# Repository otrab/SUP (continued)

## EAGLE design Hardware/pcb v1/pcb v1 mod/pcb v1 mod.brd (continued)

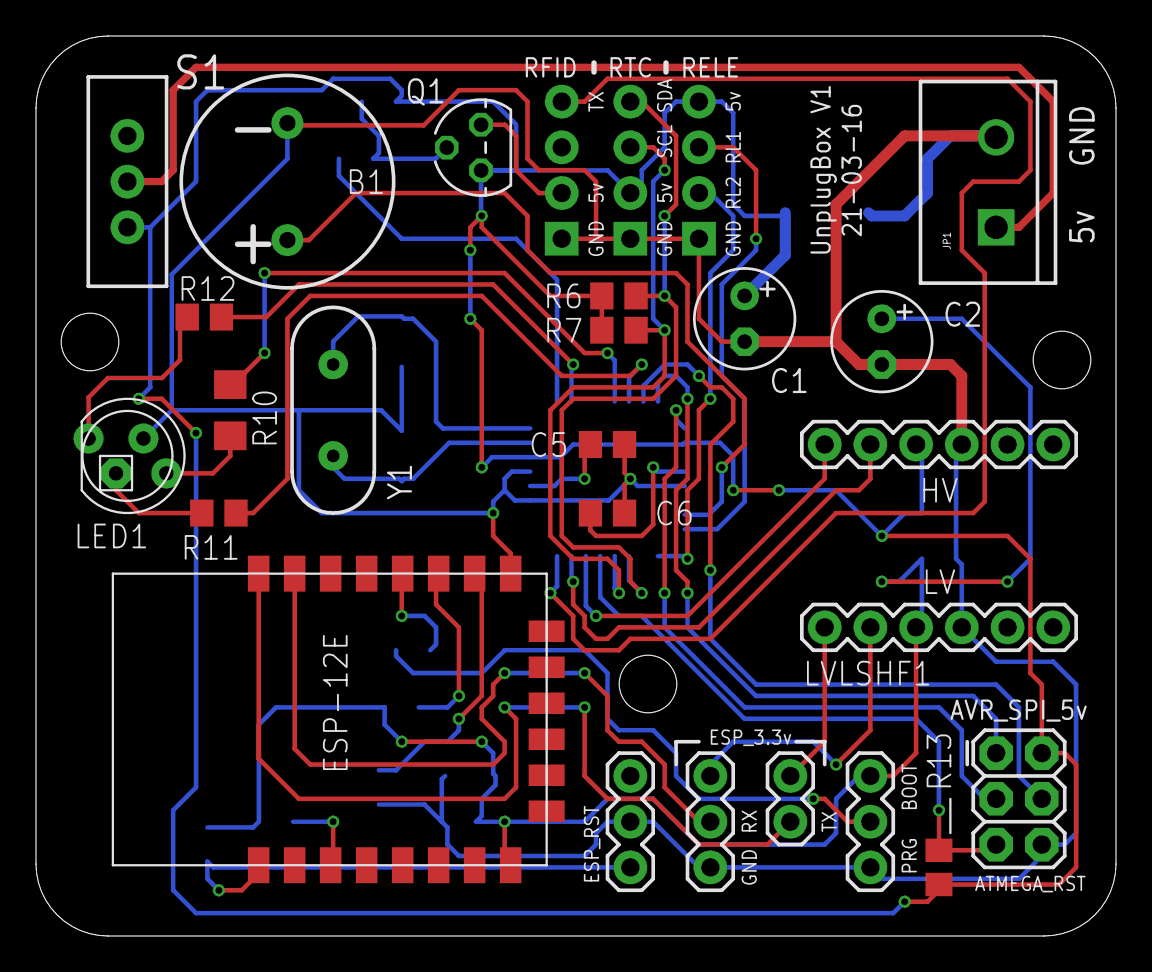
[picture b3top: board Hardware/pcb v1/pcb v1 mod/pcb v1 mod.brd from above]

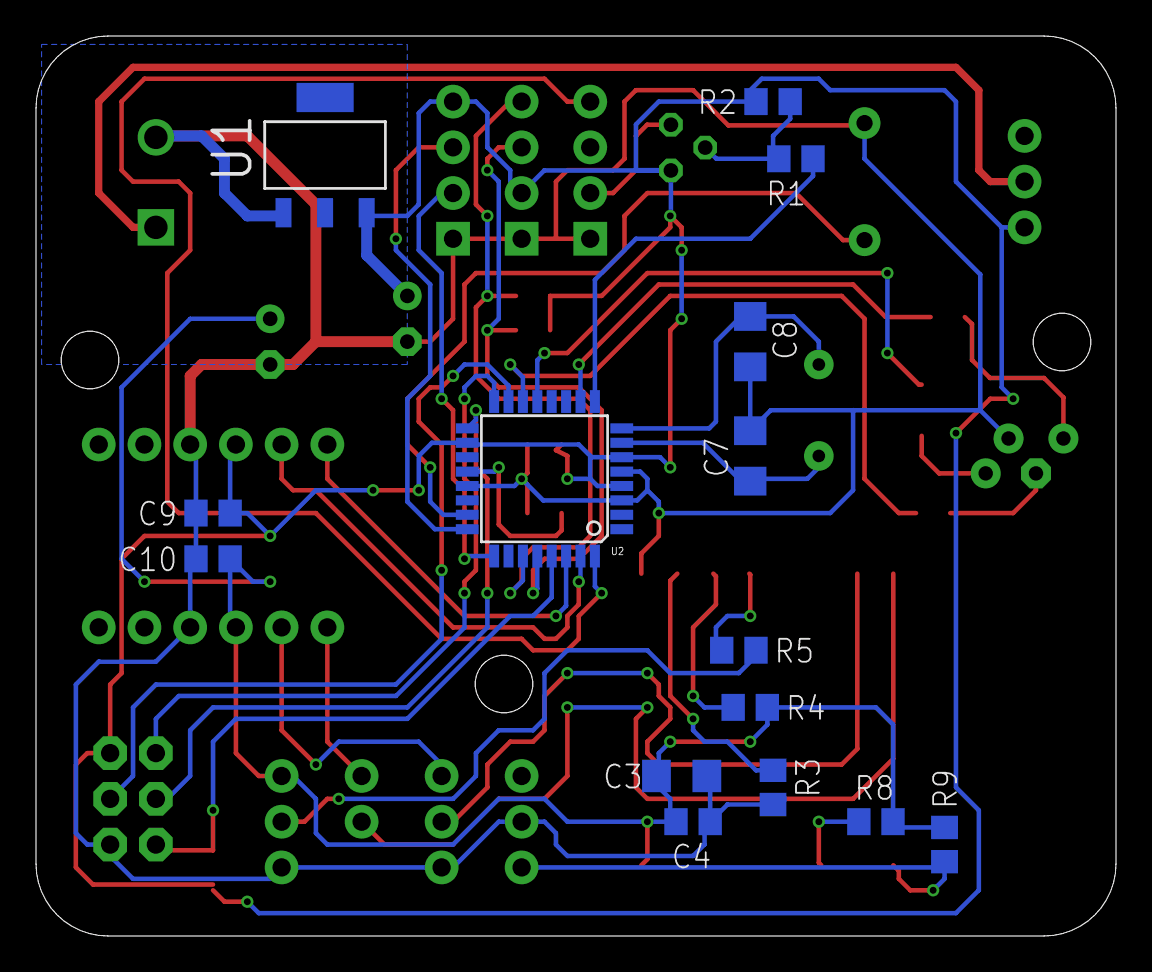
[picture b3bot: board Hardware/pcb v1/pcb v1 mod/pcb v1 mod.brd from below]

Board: 2 copper layers, 60.0 x 50.0 mm, 41 parts (15 on the bottom side), 38 nets.

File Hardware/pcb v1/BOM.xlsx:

Qty | Value | Device | Package | Parts | Description | Link
1 |  | ESP8266-12EESP8266-ESP12E | ESP8266-ESP12E | MDL1 | ESP8266-12E with additional I/O and GPIO04/05 corrected
3 |  | M03PTH | 1X03 | JP3, JP7, JP8 | Header 3
3 |  | M041X04_NO_SILK | 1X04_NO_SILK | JP2, JP4, JP5 | Header 4
1 |  | SWITCH-SPDTPTH | SWITCH-SPDT | S1 | SPDT Switch
1 | 100K | R-US_R0805 | R0805 | R13 | RESISTOR, American symbol
2 | 100R | R-US_R0805 | R0805 | R11, R12 | RESISTOR, American symbol
5 | 100nF | C-USC0805 | C0805 | C4, C5, C6, C9, C10 | CAPACITOR, American symbol
9 | 10k | R-US_R0805 | R0805 | R1, R2, R3, R4, R5, R6, R7, R8, R9 | RESISTOR, American symbol
2 | 10uF | CPOL-USE2.5-6 | E2,5-6 | C1, C2 | POLARIZED CAPACITOR, American symbol
1 | 160R | R-US_R1206 | R1206 | R10 | RESISTOR, American symbol
1 | 16Mhz | CRYSTALHC49US | HC49US | Y1 | Various standard crystals. Proven footprints. Spark Fun Electronics SKU : COM-0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
1 | 1uF | C-USC1206 | C1206 | C3 | CAPACITOR, American symbol
2 | 22pF | C-USC1206 | C1206 | C7, C8 | CAPACITOR, American symbol
1 | 2N3906 | 2N3906 | TO92 | Q1 | PNP Transistor
1 | 5MMRGBLED | 5MMRGBLED | LED5MMRGB | LED1
1 | ADP3338AKCZ-3.3RL7 | ADP3338AKCZ-3.3RL7 | SOT230P700X180-4N | U1 | Low Dropout Regulator | http://olimex.cl/en_US/shop/product/regulador-de-voltaje-adp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
1 | ATMEGA328P | ATMEGA328_SMT | TQFP32-08 | U2 | 32-Pin Atmega328 part
1 | AVR_SPI_PRG_6PTH | AVR_SPI_PRG_6PTH | 2X3 | J1 | AVR ISP 6 Pin
1 | BUZZERPTH | BUZZERPTH | BUZZER-12MM | SG1 | Buzzer 12mm
1 | LEVELSHIFTER4 | LEVELSHIFTER4 | LEVELSHIFTER4 | LVLSHF1
1 | M025MM | M025MM | SCREWTERMINAL-5MM-2 | JP1 | Standard 2-pin 0.1 header. Use with"
1 | M02PTH | M02PTH | 1X02 | JP9 | Standard 2-pin 0.1 header. Use with"

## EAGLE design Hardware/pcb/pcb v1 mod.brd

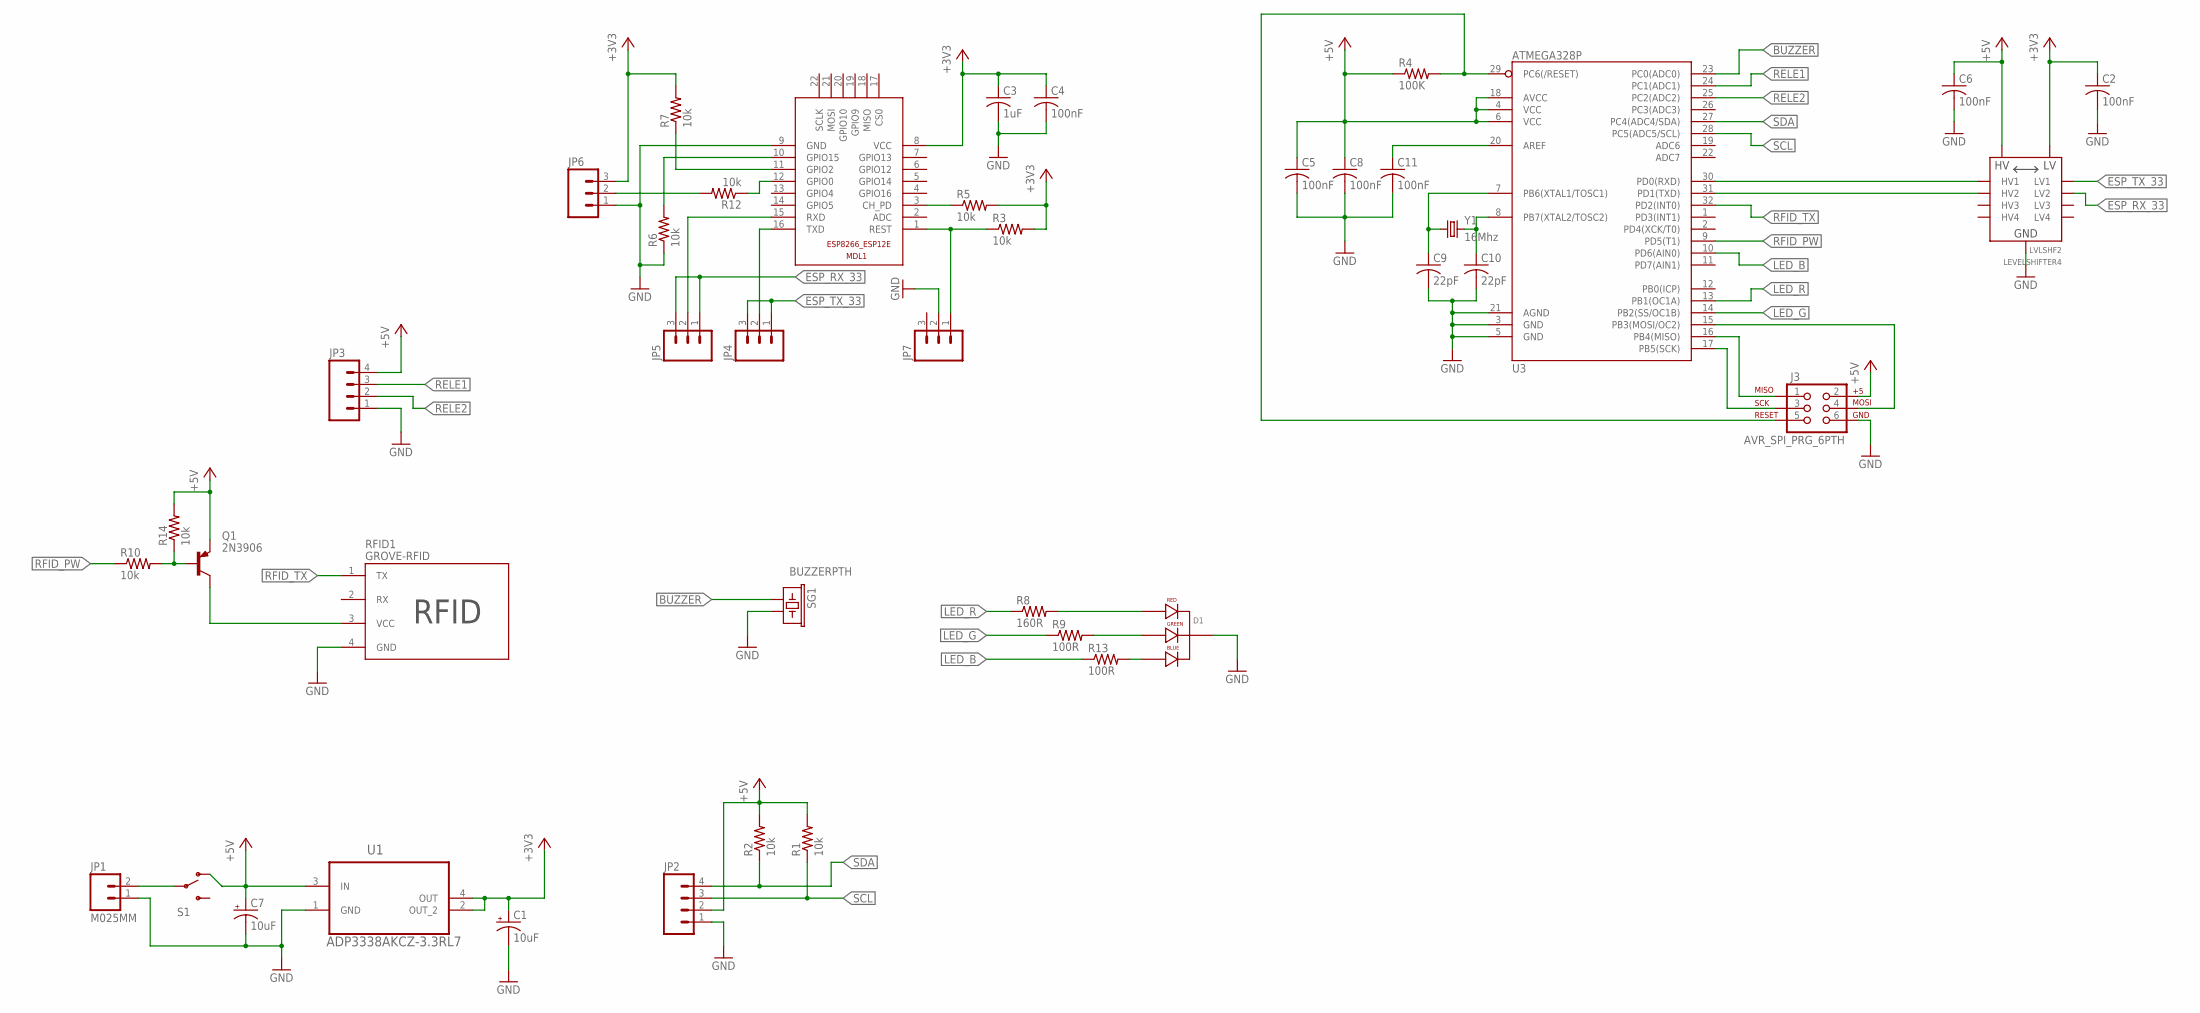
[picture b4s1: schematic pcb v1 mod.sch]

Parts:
C1, C7: 10uF; E2,5-6
C2, C4, C5, C6, C8, C11: 100nF; C0805
C3: 1uF; C1206
C9, C10: 22pF; C1206
D1: LED-RGB-CC-THRUCLEAR; LED-RGB-THRU
J3: AVR_SPI_PRG_6PTH; 2X3
JP1: M025MM; SCREWTERMINAL-5MM-2
JP2, JP3: M04PTH; 1X04
JP4, JP5, JP6, JP7: M03PTH; 1X03
LVLSHF2: LEVELSHIFTER4
MDL1: ESP8266-12EESP8266-ESP12E; ESP8266-ESP12E
Q1: 2N3906; TO92
R1, R2, R3, R5, R6, R7, R10, R12, R14: 10k; R0805
R4: 100K; R0805
R8: 160R; R1206
R9, R13: 100R; R0805
RFID1: GROVE-RFID
S1: SWITCH-SPDTPTH; SWITCH-SPDT
SG1: BUZZERPTH; BUZZER-12MM
U1: ADP3338AKCZ-3.3RL7; SOT230P700X180-4N
U3: ATMEGA328P; TQFP32-08
Y1: 16Mhz; HC49US

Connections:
+3V3: C1.+, C2.1, C3.1, C4.1, JP6.3, LVLSHF2.LV, MDL1.8 (VCC), R3.2, R5.2, R7.2, U1.2 (OUT_2), U1.4 (OUT)
+5V: C5.1, C6.1, C7.+, C8.1, J3.2, JP2.2, JP3.4, LVLSHF2.HV, Q1.3 (E), R1.2, R2.2, R4.1, R14.2, S1.1 (O), U1.3 (IN), U3.4 (VCC), U3.6 (VCC), U3.18 (AVCC)
BUZZER: SG1.+ (1), U3.23 (PC0(ADC0))
ESP_RX_33: JP5.1, JP5.3, LVLSHF2.LV2
ESP_TX_33: JP4.1, JP4.3, LVLSHF2.LV1
GND: C1.-, C2.2, C3.2, C4.2, C5.2, C6.2, C7.-, C8.2, C9.2, C10.2, C11.2, D1.2 (CATHODE), J3.6, JP1.1, JP2.1, JP3.1, JP6.1, JP7.2, LVLSHF2.GND, LVLSHF2.GND1 (GND), MDL1.9 (GND), R6.1, RFID1.4 (GND), SG1.- (2), U1.1 (GND), U3.3 (GND), U3.5 (GND), U3.21 (AGND)
LED_B: R13.1, U3.10 (PD6(AIN0))
LED_G: R9.1, U3.14 (PB2(SS/OC1B))
LED_R: R8.1, U3.13 (PB1(OC1A))
unnamed: JP1.2, S1.2
unnamed: MDL1.3 (CH_PD), R5.1
unnamed: MDL1.11 (GPIO2), R7.1
unnamed: MDL1.12 (GPIO0), R12.1
unnamed: MDL1.10 (GPIO15), R6.2
unnamed: JP5.2, MDL1.15 (RXD)
unnamed: Q1.2 (B), R10.2, R14.1
unnamed: JP4.2, MDL1.16 (TXD)
unnamed: JP7.1, MDL1.1 (REST), R3.1
unnamed: D1.1 (RED_CATHODE), R8.2
unnamed: C9.1, U3.7 (PB6(XTAL1/TOSC1)), Y1.1
unnamed: C10.1, U3.8 (PB7(XTAL2/TOSC2)), Y1.2
unnamed: C11.1, U3.20 (AREF)
unnamed: D1.3 (GREEN_CATHODE), R9.2
unnamed: D1.4 (BLUE_CATHODE), R13.2
unnamed: J3.3, U3.17 (PB5(SCK))
unnamed: J3.1, U3.16 (PB4(MISO))
unnamed: J3.4, U3.15 (PB3(MOSI/OC2))
unnamed: JP6.2, R12.2
unnamed: LVLSHF2.HV1, U3.30 (PD0(RXD))
unnamed: LVLSHF2.HV2, U3.31 (PD1(TXD))
unnamed: Q1.1 (C), RFID1.3 (VCC)
unnamed: J3.5, R4.2, U3.29 (PC6(/RESET))
RELE1: JP3.3, U3.24 (PC1(ADC1))
RELE2: JP3.2, U3.25 (PC2(ADC2))
RFID_PW: R10.1, U3.9 (PD5(T1))
RFID_TX: RFID1.1 (TX), U3.32 (PD2(INT0))
SCL: JP2.3, R1.1, U3.28 (PC5(ADC5/SCL))
SDA: JP2.4, R2.1, U3.27 (PC4(ADC4/SDA))

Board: 2 copper layers, 42 parts (0 on the bottom side), 38 nets, no tracks yet.

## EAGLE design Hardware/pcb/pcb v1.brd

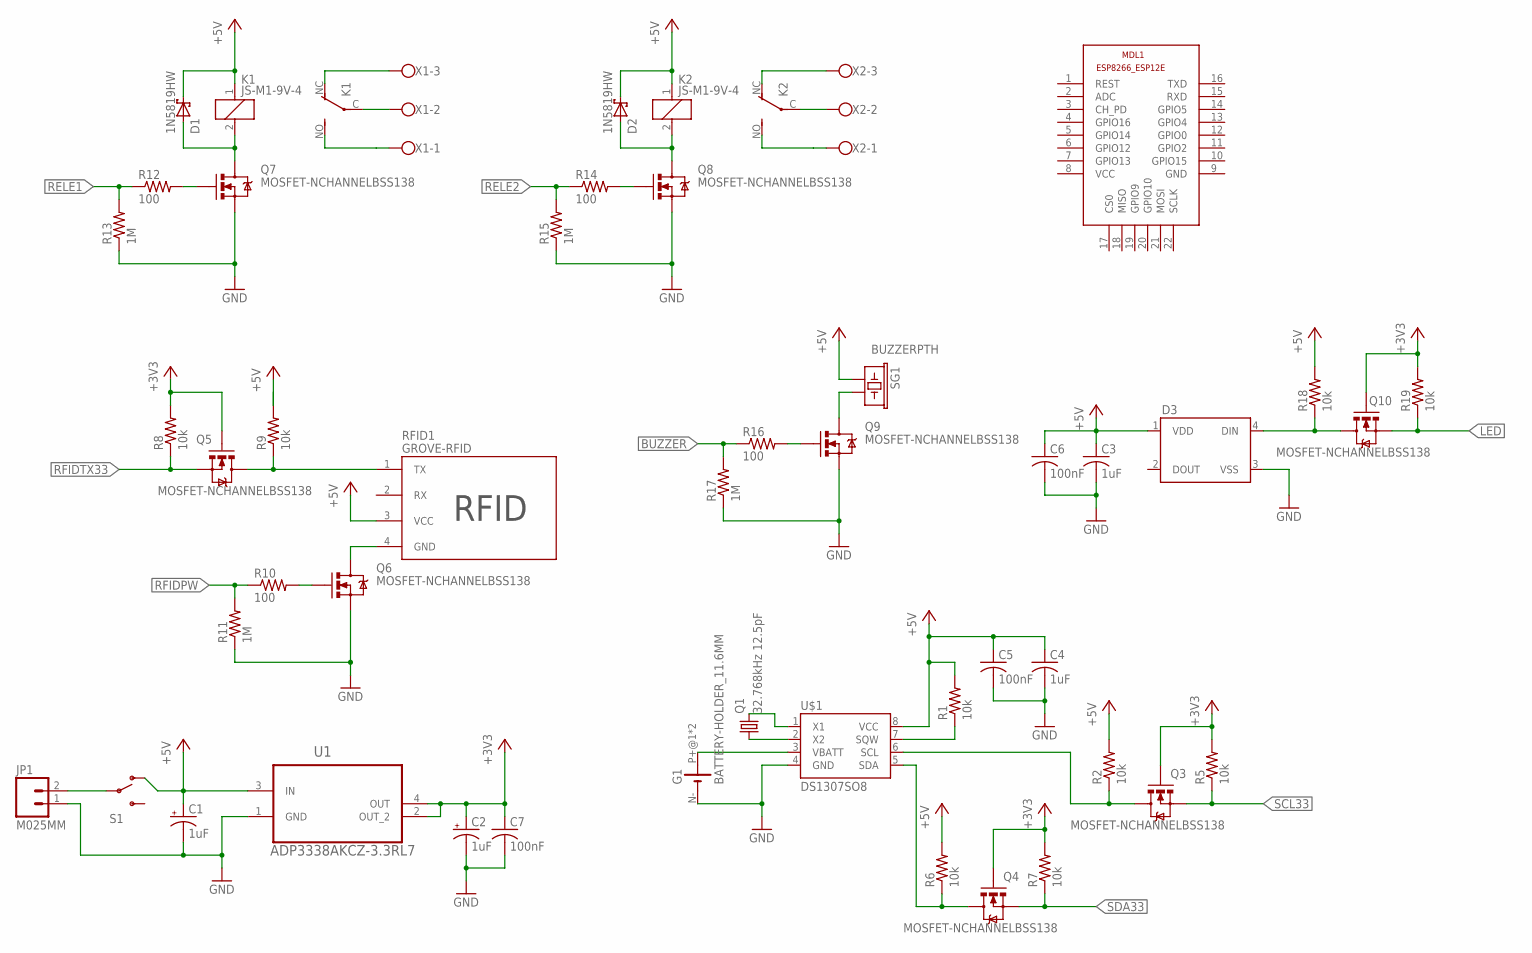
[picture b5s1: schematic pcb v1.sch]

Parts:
C1, C2: 1uF; 150CLZ-1010
C3, C4: 1uF; C0805
C5, C6, C7: 100nF; C0805
D1, D2: 1N5819HW; SOD-123
D3: WS2812B
G1: BATTERY-HOLDER_11.6MM; CELL_RETAINER_11.6MM
JP1: M025MM; SCREWTERMINAL-5MM-2
K1, K2: JS-M1-9V-4; JS-M
MDL1: ESP8266-12EESP8266-ESP12E; ESP8266-ESP12E
Q1: 32.768kHz 12.5pF; TC26H
Q3, Q4, Q5, Q6, Q7, Q8, Q9, Q10: MOSFET-NCHANNELBSS138; SOT23-3
R1, R2, R5, R6, R7, R8, R9, R18, R19: 10k; R0805
R10, R12, R14, R16: 100; R0805
R11, R13, R15, R17: 1M; R0805
RFID1: GROVE-RFID
S1: SWITCH-SPDTPTH; SWITCH-SPDT
SG1: BUZZERPTH; BUZZER-12MM
U1: ADP3338AKCZ-3.3RL7; SOT230P700X180-4N
U$1: DS1307SO8; SO08
X1, X2: W237-103

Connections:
+3V3: C2.+, C7.1, Q3.1 (G), Q4.1 (G), Q5.1 (G), Q10.1 (G), R5.2, R7.2, R8.2, R19.2, U1.2 (OUT_2), U1.4 (OUT)
+5V: C1.+, C3.1, C4.1, C5.1, C6.1, D1.C, D2.C, D3.1 (VDD), K1.1, K2.1, R1.2, R2.2, R6.2, R9.2, R18.2, RFID1.3 (VCC), S1.1 (O), SG1.+ (1), U1.3 (IN), U$1.8 (VCC)
BUZZER: R16.1, R17.2
GND: C1.-, C2.-, C3.2, C4.2, C5.2, C6.2, C7.2, D3.3 (VSS), G1.N- (-), JP1.1, Q6.2 (S), Q7.2 (S), Q8.2 (S), Q9.2 (S), R11.1, R13.1, R15.1, R17.1, U1.1 (GND), U$1.4 (GND)
LED: Q10.2 (S), R19.1
unnamed: JP1.2, S1.2
unnamed: Q1.2, U$1.1 (X1)
unnamed: Q1.1, U$1.2 (X2)
unnamed: G1.P+@1 (+), G1.P+@2 (+), U$1.3 (VBATT)
unnamed: Q3.3 (D), R2.1, U$1.6 (SCL)
unnamed: R1.1, U$1.7 (SQW)
unnamed: Q6.3 (D), RFID1.4 (GND)
unnamed: Q4.3 (D), R6.1, U$1.5 (SDA)
unnamed: Q5.3 (D), R9.1, RFID1.1 (TX)
unnamed: D1.A, K1.2, Q7.3 (D)
unnamed: Q6.1 (G), R10.2
unnamed: Q7.1 (G), R12.2
unnamed: K1.NC (O), X1.3
unnamed: K1.C, X1.2
unnamed: K1.NO (S), X1.1
unnamed: D2.A, K2.2, Q8.3 (D)
unnamed: Q8.1 (G), R14.2
unnamed: K2.NC (O), X2.3
unnamed: K2.C, X2.2
unnamed: K2.NO (S), X2.1
unnamed: Q9.1 (G), R16.2
unnamed: Q9.3 (D), SG1.- (2)
unnamed: D3.4 (DIN), Q10.3 (D), R18.1
RELE1: R12.1, R13.2
RELE2: R14.1, R15.2
RFIDPW: R10.1, R11.2
RFIDTX33: Q5.2 (S), R8.1
SCL33: Q3.2 (S), R5.1
SDA33: Q4.2 (S), R7.1

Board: 2 copper layers, 48 parts (0 on the bottom side), 34 nets, no tracks yet.

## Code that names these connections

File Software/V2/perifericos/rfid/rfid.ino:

#include <SPI.h>
#include "MFRC522.h"
#include <SoftwareSerial.h>

SoftwareSerial debugSerial(PD3, PD4);

#define RFID_SS_3V3 PB0
#define RFID_OC_NRST PD7

MFRC522 rfid(RFID_SS_3V3, RFID_OC_NRST); // Instance of the class

// Init array that will store new NUID
byte nuidPICC[4];

void setup() {
  debugSerial.begin(115200);
  SPI.begin(); // Init SPI bus
  rfid.PCD_Init(); // Init MFRC522
}

void loop() {

  // Look for new cards
  if ( ! rfid.PICC_IsNewCardPresent())
    return;

  // Verify if the NUID has been readed
  if ( ! rfid.PICC_ReadCardSerial())
    return;

  if (rfid.uid.uidByte[0] != nuidPICC[0] ||
    rfid.uid.uidByte[1] != nuidPICC[1] ||
    rfid.uid.uidByte[2] != nuidPICC[2] ||
    rfid.uid.uidByte[3] != nuidPICC[3] ) {
    debugSerial.println(F("A new card has been detected."));

    // Store NUID into nuidPICC array
    for (byte i = 0; i < 4; i++) {
      nuidPICC[i] = rfid.uid.uidByte[i];
    }

    debugSerial.println(F("The NUID tag is:"));
    debugSerial.print(F("In hex: "));
    printHex(rfid.uid.uidByte, rfid.uid.size);
    debugSerial.println();
  }
  else {
      debugSerial.println(F("Card read previously."));
      rfid.PCD_Init();
      return;
  }

  // Halt PICC
  rfid.PICC_HaltA();

  // Stop encryption on PCD
  rfid.PCD_StopCrypto1();
}


/**
 * Helper routine to dump a byte array as hex values to Serial.
 */
void printHex(byte *buffer, byte bufferSize) {
  for (byte i = 0; i < bufferSize; i++) {
    debugSerial.print(buffer[i] < 0x10 ? " 0" : " ");
    debugSerial.print(buffer[i], HEX);
  }
}

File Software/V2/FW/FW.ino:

#include "RTClib.h"
#include <SoftwareSerial.h>

#define RFID_SS_3V3 8
#define RFID_OC_NRST 7
#define BUZZER A0
#define RELE A1
#define BOTON A7

SoftwareSerial debugSerial(3, 4);

void setup() {
	debugSerial.begin(115200);
}
enum Estado {bloqueado, desbloqueado, user, master};
Estado estado = bloqueado;

class Usuario {
public:
	Usuario() {
		id = 66;
	}
	byte id;
	byte master;
	byte nuidPICC[4];
	DateTime horario_inicio;
	DateTime horario_fin;
};

boolean intervalo_t(DateTime t, DateTime ti, DateTime tf) {
	return (t.hh > ti.hh || t.mm > ti.mm || t.ss > ti.ss)
	       && (t.hh < tf.hh || t.mm < tf.mm || t.ss < tf.ss);
}
boolean check_nuid(byte * nuid1, byte * nuid2) {
	return nuid1[0] != nuid2[0]
	       || nuid1[1] != nuid2[1]
	       || nuid1[2] != nuid2[2]
	       || nuid1[3] != nuid2[3];
}
boolean leer_tarjeta() {
	if(rfid.PICC_IsNewCardPresent()) {
		if(rfid.PICC_ReadCardSerial()) {
			return 1;
		}
	}
	return 0;
}

byte nusers=4;
Usuario users[4];
DateTime tiempo;

void loop() {
    //Lecturas de tarjetas, tiempo del RTC, etc...
	tarjeta = leer_tarjeta();
    //Transiciones de estados, no leer nada aqui, usar solo variables fijas.
	if(estado == bloqueado) {
        //Para cada usuario...
		for(int i = 0; i < nusers; i++) {
            //Ignorar usuarios no creados.
			if(users[i].id != 0) {
                //Transicion a horario permitido
				if(intervalo_t(tiempo, users[i].horario_inicio, users[i].horario_fin)) {
					estado = desbloqueado;
				}
                //Si hay tarjeta puesta...
				if(tarjeta) {
                    //Revisar de quien es la tarjeta
					if(check_nuid(rfid.uid.uidByte, users[i].nuidPICC)) {
                        //Transicion a modo master o revisar el tiempo restante del ninho
						if(users[i].master) {
							estado = master;
						} else {
                            //Revisar el tiempo restante
						}
					}
				}
			}
		}
	} else if(estado == desbloqueado) {
	} else if(estado == user) {
	} else if(estado == master) {
	}
}

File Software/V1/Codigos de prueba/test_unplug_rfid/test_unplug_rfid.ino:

#include <SoftwareSerial.h>
#define RFID_TX 2
#define RFID_PW 5
#define RELE2 A2

SoftwareSerial debugSerial(A3, RELE2);
SoftwareSerial rfidSerial(RFID_TX, A6);

void setup() {
  // put your setup code here, to run once:
  debugSerial.begin(115200);
  rfidSerial.begin(9600);
  pinMode(RFID_PW,OUTPUT);
}

void loop() {
  debugSerial.println("rfid on");
  // put your main code here, to run repeatedly:
  digitalWrite(RFID_PW,LOW);
  unsigned long t1=millis();
  while(millis()-t1<5000){
    if(rfidSerial.available()>0){
      debugSerial.write(rfidSerial.read());
    }
  }
  debugSerial.println("rfid off");
  digitalWrite(RFID_PW,HIGH);
  delay(5000);
}

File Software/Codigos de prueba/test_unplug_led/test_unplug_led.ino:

#define LED_B 6
#define LED_G 10
#define LED_R 9
void setup() {
  pinMode(LED_B, OUTPUT);
  pinMode(LED_G, OUTPUT);
  pinMode(LED_R, OUTPUT);
  digitalWrite(LED_R, LOW);
  digitalWrite(LED_G, LOW);
  digitalWrite(LED_B, LOW);
}

void loop() {
  // put your main code here, to run repeatedly
  digitalWrite(LED_R, HIGH);
  digitalWrite(LED_G, LOW);
  digitalWrite(LED_B, LOW);
  delay(1000);
  digitalWrite(LED_R, LOW);
  digitalWrite(LED_G, HIGH);
  digitalWrite(LED_B, LOW);
  delay(1000);
  digitalWrite(LED_R, LOW);
  digitalWrite(LED_G, LOW);
  digitalWrite(LED_B, HIGH);
  delay(1000);
  digitalWrite(LED_R, LOW);
  digitalWrite(LED_G, LOW);
  digitalWrite(LED_B, LOW);
}

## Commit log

2016-03-10 hello world
2016-03-16 probando
2016-03-16 PCB version 1
2016-03-16 Añadir partes y gitignore
2016-03-17 Perifericos agregados
    Modulo Grove RFID
    RTC
    2 Reles
    Regulador 3.3v
    Buzzer
    LED RGB
2016-03-17 Versión modular
2016-03-17 Quitar el rtc
2016-03-18 Modulo reles
2016-03-20 esp y atmega328
2016-03-21 Esquematico completo
2016-03-21 Ruteo completo
2016-03-21 documentacion
2016-03-21 Correcciones placa
2016-03-22 Cambios menores
2016-03-22 BOM excel
    Falta agregar link proveedores
2016-03-22 Arreglo alineacion gerber
2016-03-29 Agregada la sección Software, con algunos módulos de prueba en Firmware.
2016-03-29 agregada información sobre el IDE en el readme.txt
2016-03-30 Ordene todo el contenido de la carpeta Software y agregue la libreria Metro como local en box_atmega_v00. Este ultimo ahora es compilable
2016-03-30 comentarios mejorados en box_atmega_v00.ino
2016-04-01 Se cambiaron pines y se inviertieron el sentido del rele y del transistor al rfid.
2016-04-02 Version preparada para Arduino Day. Se incluyo LED RGB y sonido. Tiempo por defecto 5 minutos.
2016-04-02 Agregado bip entre cada minuto.
2016-04-08 Cambio de valores de condensadores
2016-04-10 dibujos de las dimensiones de las placas
2016-04-12 Cambios en algunas resistencias
2016-04-14 cambio resistencia led
2016-04-16 atmega328 qtfp pinout
2016-04-18 test
2016-04-18 La v01 del atmega tiene los pines actuales de la placa de Diego.
2016-04-18 Se agrego el pin A2 al sw serial del RFID para debuggear.
2016-04-19 códigos de prueba
2016-04-21 Cambio valor C3
2016-04-21 cambio prueba buzzer
2016-05-10 pcb v2 atmega y rtc
2016-05-10 actualización gitignore
2016-05-10 eliminación lcks
2016-05-10 pcb v2 buzzer
2016-05-11 pcb v2 rfid
2016-05-12 libreria AD8192
2016-05-12 libreria TXS0108E
2016-05-13 avances pcb v2
2016-05-13 v2 esquematico semiterminado
2016-05-13 fram
2016-05-17 v2 esquematico completo
2016-05-17 Comienzo ruteo
2016-05-19 empaquetados
2016-05-20 posiciones componentes externos
2016-05-20 ruteo tdms
2016-05-20 ruteo hdmi completo
2016-05-22 avance ruteo
2016-05-23 ruteo completo
    falta arreglar la serigrafia
2016-05-23 gerbers y render
    falta arreglar la serigrafia
2016-05-23 Serigrafia arreglada
2016-05-24 documentación para diseño
2016-05-26 bom y cambios menores en la pcb
2016-05-26 bom actualizado y con códigos
2016-05-27 switch
2016-05-30 cambio de boton
2016-05-30 arreglo serigrafia
2016-06-01 Orden e Inicio por parte de SS Firmware
2016-06-01 Boton conectado al esp
2016-06-01 bordes redondeados
2016-06-02 arreglo dimension
2016-06-02 itead
2016-06-02 arreglo gerber itead
2016-06-03 esquematico actualizado
2016-06-08 pines
2016-06-09 gerber osh park
2016-06-10 Documentación pines
2016-07-01 FW test
2016-07-01 revertir los cambios de osh park
2016-07-02 pcb V2r1
    Gerbers de itead y seeedstudio actualizados
2016-07-05 cambios bom
2016-07-05 arreglo hdmi v2r1
2016-07-12 Comienzo pcb V3
2016-07-13 rtc y led V3
2016-07-13 esquematico y bom v3 completo
2016-07-20 Inicio nuevo firmware
2016-07-20 Ruteo pcb V3 completo
2016-07-29 logos
    tipografia con logo
    22EE: Logo / Fill & text
    22EF: Logo / Fill & no text
    22F0: Logo / Outline & no text
    22F1: Logo / Outline & text
2016-07-29 gerbers v3
2016-07-29 gerbers v3 itead
2016-08-04 bom v3 actualizado
